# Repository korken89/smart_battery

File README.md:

# Testing repository for components of the Smart Charger project

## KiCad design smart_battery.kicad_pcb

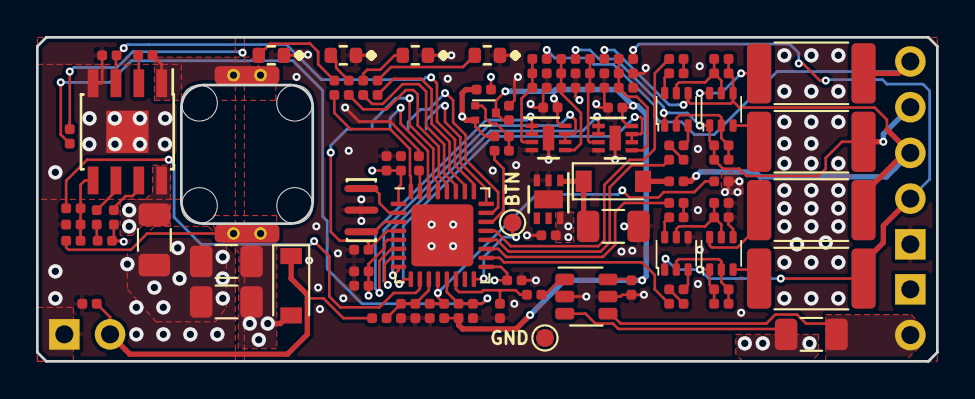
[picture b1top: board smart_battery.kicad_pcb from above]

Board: 4 copper layers, 50.0 x 18.0 mm, 102 parts (1 on the bottom side), 74 nets.

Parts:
C101, C102, C104, C106, C108, C109, C110, C111, C114, C201, C202, C203, C204, C205, C206, C207, C208, C209, C210, C211, C212, C213, C214, C301, C304: 0.1u; C_0402_1005Metric_Rounded
C103, C302, C305, C306: 22u; C_1206_3216Metric
C105, C107, C112, C113: 4.7u; C_0402_1005Metric_Rounded
C303: 2.7n; C_0402_1005Metric_Rounded
D101, D301: MBR0580S1-7; D_SOD-123
D102, D103, D104, D105: LED_Small; LEDC1608X60
D201, D202: BAT54SDW; SOT-363
FB101, FB102: BKH1005LM182-T; R_0402_1005Metric_Rounded
J101, J102: Conn_01x02_Male; 1x2_2.54mm
J103: Conn_01x05_Male; 1x5_2.54mm
J104: Dronecode_Debug; jst-sh-hor-6
J105, J106: Conn_01x01_Male; TestPoint_Pad_D1.0mm
L301: 10u; ASPI-0630LR-HOLE
Q101: RZM001P02T2L; SOT-723
Q201, Q202: PMGD280UN,115; SOT-363
R101, R102, R106, R304: 18k; R_0402_1005Metric_Rounded
R103: 50m; R_1206_3216Metric
R104, R213, R215, R217, R219: 1M; R_0402_1005Metric_Rounded
R105: 150k; R_0402_1005Metric_Rounded
R107, R109, R110, R111, R112, R113, R306: 2.5k; R_0402_1005Metric_Rounded
R108, R205, R206, R207, R208, R214, R216, R218, R220: 220k; R_0402_1005Metric_Rounded
R201, R202, R203, R204: 1k; R_0402_1005Metric_Rounded
R209, R210, R211, R212: 33; R_2512_6332Metric
R301, R302, R305: 47k; R_0402_1005Metric_Rounded
R303: 91k; R_0402_1005Metric_Rounded
TH101, TH102: 10k; R_0402_1005Metric_Rounded
U101: NCP716; DFN-6-1EP_2x2mm_P0.65mm_EP1x1.6mm
U102: STM32F051K6Ux; QFN-32-1EP_5x5mm_P0.5mm_EP3.45x3.45mm
U103: INA181; SOT-23-6
U202, U203: TSV912IQ2T; DFN-8-1EP_2x2mm_P0.45mm_EP0.64x1.38mm
U301: RT2862; SOIC-8-1EP_3.9x4.9mm_P1.27mm_EP2.35x2.35mm
Y101: PRQC8.00CR1010V00L; Resonator_3pin_3.2x1.3mm

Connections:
+3.3VA: C111.1, C112.1, FB101.2, Q101.2, R108.1, U102.5
+3V3: C105.1, C107.1, C109.1, C110.1, FB101.1, U101.6, U102.1, U102.17
/AMPS_ONOFF: R107.2, U102.22
/AMP_PWR: C104.2, C113.1, C213.2, C214.2, Q101.3, R101.2, R102.2, U103.6, U202.8, U203.8
/BAL1: R204.2, U102.18
/BAL2: R203.2, U102.19
/BAL3: R202.2, U102.20
/BAL4: R201.2, U102.21
/BATTERY: J101.2, R103.1, U103.4
/BOOT0: R106.1, U102.31
/BTN: J106.1, U102.16
/CELL1: C207.1, D202.1, J103.2, Q202.1, R207.2, R212.2, R213.2
/CELL2: C206.1, D201.4, FB102.2, J103.3, Q201.4, R206.2, R211.2, R215.2
/CELL3: C205.1, D201.1, J103.4, Q201.1, R205.2, R210.2, R217.2
/CELL4: J103.5, R209.2, R219.2
/DCDC_ENABLE: R301.2, U102.25, U301.3
/I_CHG: C114.2, R113.1, U102.14
/LED1: R109.1, U102.32
/LED2: R112.1, U102.28
/LED3: R111.1, U102.27
/LED4: R110.1, U102.26
/RST: C108.2, J104.1, U102.4
/RX: J104.3, U102.30
/SWCLK: J104.5, U102.24
/SWDIO: J104.4, U102.23
/TEMP1: C101.2, R101.1, TH101.1, U102.12
/TEMP2: C102.2, R102.1, TH102.1, U102.13
/TX: J104.2, U102.29
/VCELL1: U102.9, U203.6, U203.7
/VCELL2: U102.8, U203.1, U203.2
/VCELL3: U102.7, U202.6, U202.7
/VCELL4: U102.6, U202.1, U202.2
/VIN_CHG: C301.2, C302.2, D301.1, J102.2, R104.2, U301.8
/VIN_CHG_MEAS: C106.2, R104.1, R105.2, U102.11
/VSET: R304.2, U102.10
/buck_charger/BOOT: C304.2, U301.2
/buck_charger/COMP: C303.1, U301.6
/buck_charger/FB: R304.1, R305.2, R306.2, U301.5
/buck_charger/OUT_CHARGER: C305.2, C306.2, D301.2, L301.2, R103.2, R305.1, U103.3
/buck_charger/SW: C304.1, L301.1, U301.1
/cell_measurement_and_balancing/CELL1_G: C208.2, D202.5, Q202.5, R208.1
/cell_measurement_and_balancing/CELL2_G: C207.2, D202.2, Q202.2, R207.1
/cell_measurement_and_balancing/CELL3_G: C206.2, D201.5, Q201.5, R206.1
/cell_measurement_and_balancing/CELL4_G: C205.2, D201.2, Q201.2, R205.1
/cell_measurement_and_balancing/VCELL1: C209.2, R213.1, R214.2, U203.5
/cell_measurement_and_balancing/VCELL2: C210.2, R215.1, R216.2, U203.3
/cell_measurement_and_balancing/VCELL3: C211.2, R217.1, R218.2, U202.5
/cell_measurement_and_balancing/VCELL4: C212.2, R219.1, R220.2, U202.3
GND: C101.1, C102.1, C103.1, C104.1, C105.2, C106.1, C107.2, C108.1, C109.2, C110.2, C111.2, C112.2, C113.2, C114.1, C208.1, C209.1, C210.1, C211.1, C212.1, C213.1, C214.1, D102.1, D103.1, D104.1, D105.1, D202.4, J103.1, J104.0, J104.6, J105.1, Q202.4, R105.1, R106.2, R208.2, R214.1, R216.1, R218.1, R220.1, TH101.2, TH102.2, U101.2, U101.3, U101.7, U102.33, U103.2, U103.5, U202.4, U202.9, U203.4, U203.9, Y101.2
GNDPWR: C301.1, C302.1, C305.1, C306.1, J101.1, J102.1, R301.1, R302.2, R303.2, R306.1, U301.4, U301.9
unnamed: C103.2, D101.1, U101.1
unnamed: C201.1, R201.1
unnamed: C201.2, D201.6
unnamed: C202.1, R202.1
unnamed: C202.2, D201.3
unnamed: C203.1, R203.1
unnamed: C203.2, D202.6
unnamed: C204.1, R204.1
unnamed: C204.2, D202.3
unnamed: C303.2, R302.1
unnamed: D101.2, FB102.1
unnamed: D102.2, R109.2
unnamed: D103.2, R110.2
unnamed: D104.2, R111.2
unnamed: D105.2, R112.2
unnamed: Q101.1, R107.1, R108.2
unnamed: Q201.3, R210.1
unnamed: Q201.6, R209.1
unnamed: Q202.3, R212.1
unnamed: Q202.6, R211.1
unnamed: R113.2, U103.1
unnamed: R303.1, U301.7
unnamed: U102.2, Y101.1
unnamed: U102.3, Y101.3

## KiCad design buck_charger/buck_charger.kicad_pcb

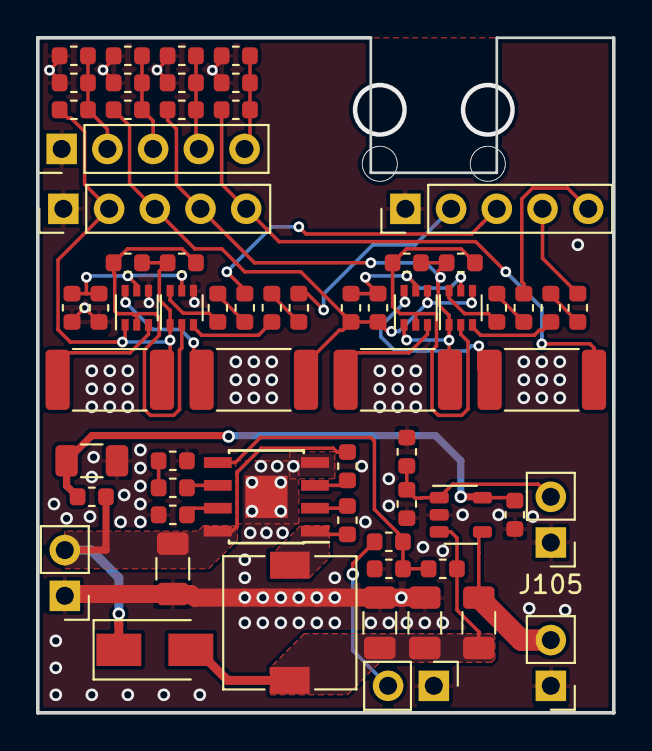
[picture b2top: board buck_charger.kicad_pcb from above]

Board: 2 copper layers, 32.0 x 37.5 mm, 64 parts (0 on the bottom side), 42 nets.

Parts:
C101, C104, C105, C106: 22u; C_1206_3216Metric
C102: 2.7n; C_0603_1608Metric
C103, C107, C108, C109, C110, C111, C112, C113, C114, C115, C116, C117, C118, C119, C120: 0.1u; C_0603_1608Metric
D101: VSSAF56-M3/6A; D_SMA
D102, D103: BAT54SDW; SOT-363_SC-70-6
J101, J102, J104, J105: Conn_01x02_Male; PinHeader_1x02_P2.54mm_Vertical
J103, J106, J107: Conn_01x05; PinHeader_1x05_P2.54mm_Vertical
L101: 10u; L_7.3x7.3_H3.5
Q101, Q102: PMGD280UN,115; SOT-363_SC-70-6
R101, R103, R108, R110, R116, R117, R118, R119, R125, R127, R129: 100k; R_0603_1608Metric
R102, R105: 47k; R_0603_1608Metric
R104: 18k; R_0603_1608Metric
R106: 2.5k; R_0603_1608Metric
R107: 50m; R_1206_3216Metric
R109, R124, R126, R128: 470k; R_0603_1608Metric
R111: 10; R_0603_1608Metric
R112, R113, R114, R115: 1k; R_0603_1608Metric
R120, R121, R122, R123: 33; R_2512_6332Metric
U101: RT2862; SOIC-8-1EP_3.9x4.9mm_P1.27mm_EP2.35x2.35mm
U102: INA138; SOT-23-5

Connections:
/BOOT: C103.2, U101.2
/CELL1: C116.1, D103.1, J106.2, Q102.1, R118.2, R123.2, R128.2
/CELL1_G: C117.2, D103.5, Q102.5, R119.1
/CELL2: C115.1, D102.4, J106.3, Q101.4, R117.2, R122.2, R126.2
/CELL2_G: C116.2, D103.2, Q102.2, R118.1
/CELL3: C114.1, D102.1, J106.4, Q101.1, R116.2, R121.2, R124.2
/CELL3_G: C115.2, D102.5, Q101.5, R117.1
/CELL4: J106.5, R109.2, R120.2
/CELL4_G: C114.2, D102.2, Q101.2, R116.1
/CHG_OUT: C104.2, C106.2, D101.2, L101.2, R105.1, R107.2, U102.3
/COMP: C102.1, U101.6
/DRIVE1: J103.2, R115.2
/DRIVE2: J103.3, R114.2
/DRIVE3: J103.4, R113.2
/DRIVE4: J103.5, R112.2
/FB: R104.1, R105.2, R106.2, U101.5
/IMEAS: C108.2, J105.2, R108.2, U102.1
/SW: C103.1, L101.1, U101.1
/VCELL1: C120.2, J107.2, R128.1, R129.2
/VCELL2: C119.2, J107.3, R126.1, R127.2
/VCELL3: C118.2, J107.4, R124.1, R125.2
/VCELL4: C109.2, J107.5, R109.1, R110.2
/VIN: C101.2, D101.1, J101.2, R101.1, R111.1, U101.8
/VOUT: J104.2, R107.1, U102.4
/VSET: J102.2, R104.2
GND: C101.1, C104.1, C105.1, C106.1, C107.1, C108.1, C109.1, C117.1, C118.1, C119.1, C120.1, D103.4, J101.1, J102.1, J103.1, J104.1, J105.1, J106.1, J107.1, Q102.4, R102.2, R103.2, R106.1, R108.1, R110.1, R119.2, R125.1, R127.1, R129.1, U101.4, U101.9, U102.2
unnamed: C102.2, R102.1
unnamed: C105.2, C107.2, R111.2, U102.5
unnamed: C110.1, R112.1
unnamed: C110.2, D102.6
unnamed: C111.1, R113.1
unnamed: C111.2, D102.3
unnamed: C112.1, R114.1
unnamed: C112.2, D103.6
unnamed: C113.1, R115.1
unnamed: C113.2, D103.3
unnamed: Q101.3, R121.1
unnamed: Q101.6, R120.1
unnamed: Q102.3, R123.1
unnamed: Q102.6, R122.1
unnamed: R101.2, U101.3
unnamed: R103.1, U101.7

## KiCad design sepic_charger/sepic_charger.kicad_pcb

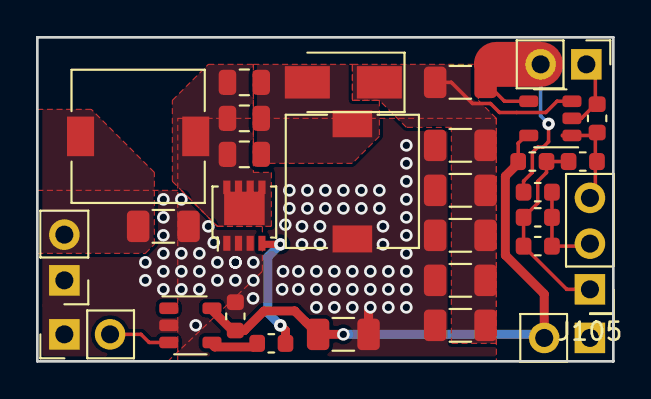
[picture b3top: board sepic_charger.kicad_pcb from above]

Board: 2 copper layers, 32.0 x 18.0 mm, 30 parts (0 on the bottom side), 12 nets.

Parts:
C1, C105, C111, C112: 0.1u; C_0603_1608Metric
C101, C106, C107, C108, C109, C110, C113: 22u; C_1206_3216Metric
C102, C103, C104: 4.7u; C_0805_2012Metric
D101: VSSAF56-M3/6A; D_SMA
J101, J102, J104, J106: Conn_01x02_Male; PinHeader_1x02_P2.54mm_Vertical
J105: Conn_01x03_Male; PinHeader_1x03_P2.54mm_Vertical
L101, L102: 10u; L_7.3x7.3_H3.5
Q101: NVTFS5C673NLTAG; LFPAK33
R1, R104: 100k; R_0603_1608Metric
R2: 22k; R_0603_1608Metric
R101: 2.2; R_0603_1608Metric
R103: 50m; R_1206_3216Metric
U101: INA138; SOT-23-5
U102: UCC2751x; SOT-23-5

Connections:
+5V: C105.1, C111.2, C113.2, J106.2, U101.5, U102.5
/GATE: Q101.4, R101.1
/IMEAS: C112.2, J105.3, R104.2, U101.1
/SEPIC_OUT: C106.2, C107.2, C108.2, C109.2, C110.2, D101.1, R103.2, U101.3
/SW: C102.2, C103.2, C104.2, L101.2, Q101.5
/SW2: C102.1, C103.1, C104.1, D101.2, L102.1
/VIN: C101.2, J101.2, L101.1
/VMEAS: C1.2, J105.2, R1.1, R2.2
/VOUT: J104.2, R1.2, R103.1, U101.4
GND: C1.1, C101.1, C105.2, C106.1, C107.1, C108.1, C109.1, C110.1, C111.1, C112.1, C113.1, J101.1, J102.1, J104.1, J105.1, J106.1, L102.2, Q101.1, Q101.2, Q101.3, R2.1, R104.1, U101.2, U102.2
unnamed: J102.2, U102.3
unnamed: R101.2, U102.4

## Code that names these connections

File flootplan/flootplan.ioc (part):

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Mcu.Name=STM32F051K8Ux
Mcu.Package=UFQFPN32
Mcu.UserName=STM32F051K8Ux
PA0.GPIOParameters=GPIO_Label
PA0.GPIO_Label=VCELL (AIN0)
PA0.Mode=IN0
PA0.Signal=ADC_IN0
PA1.GPIOParameters=GPIO_Label
PA1.GPIO_Label=VCELL (AIN1)
PA1.Mode=IN1
PA1.Signal=ADC_IN1
PA10.GPIOParameters=GPIO_Label
PA10.GPIO_Label=BAL (TIM1_CH3)
PA10.Signal=S_TIM1_CH3
PA11.GPIOParameters=GPIO_Label
PA11.GPIO_Label=BAL (TIM1_CH4)
PA11.Signal=S_TIM1_CH4
PA13.Mode=Serial_Wire
PA13.Signal=SYS_SWDIO
PA14.Mode=Serial_Wire
PA14.Signal=SYS_SWCLK
PA2.GPIOParameters=GPIO_Label
PA2.GPIO_Label=VCELL (AIN2)
PA2.Mode=IN2
PA2.Signal=ADC_IN2
PA3.GPIOParameters=GPIO_Label
PA3.GPIO_Label=VCELL (AIN3)
PA3.Mode=IN3
PA3.Signal=ADC_IN3
PA4.GPIOParameters=GPIO_Label
PA4.GPIO_Label=VSET (DAC1)
PA4.Signal=COMP_DAC11_group
PA5.GPIOParameters=GPIO_Label
PA5.GPIO_Label=VIN_CHG (AIN5)
PA5.Mode=IN5
PA5.Signal=ADC_IN5
PA6.GPIOParameters=GPIO_Label
PA6.GPIO_Label=I_CHG (AIN6)
PA6.Mode=IN6
PA6.Signal=ADC_IN6
PA7.GPIOParameters=GPIO_Label
PA7.GPIO_Label=TEMP1 (AIN7)
PA7.Mode=IN7
PA7.Signal=ADC_IN7
PA8.GPIOParameters=GPIO_Label
PA8.GPIO_Label=BAL (TIM1_CH1)
PA8.Signal=S_TIM1_CH1
PA9.GPIOParameters=GPIO_Label
PA9.GPIO_Label=BAL (TIM1_CH2)
PA9.Signal=S_TIM1_CH2
PB0.GPIOParameters=GPIO_Label
PB0.GPIO_Label=TEMP2 (AIN8)
PB0.Mode=IN8
PB0.Signal=ADC_IN8
PB1.GPIOParameters=GPIO_Label
PB1.GPIO_Label=TEMP3 (AIN9)
PB1.Mode=IN9
PB1.Signal=ADC_IN9
PB6.Mode=Asynchronous
PB6.Signal=USART1_TX
PB7.Mode=Asynchronous
PB7.Signal=USART1_RX
PB8.Signal=S_TIM16_CH1
PF0-OSC_IN.Mode=HSE-External-Oscillator
PF0-OSC_IN.Signal=RCC_OSC_IN
PF1-OSC_OUT.Mode=HSE-External-Oscillator
PF1-OSC_OUT.Signal=RCC_OSC_OUT
RCC.SYSCLKFreq_VALUE=8000000
RCC.SYSCLKSource=RCC_SYSCLKSOURCE_HSE
board=custom

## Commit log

2018-11-22 Updated design
2018-11-22 Minor changes
2018-12-12 Started buck version
2018-12-13 Updated sub modules
2018-12-13 More stuff
2019-01-03 Schematic done
2019-01-03 Added PCB
2019-01-03 Layer, track and mask setup
2019-01-03 Floorplan update
2019-01-07 More work
2019-01-08 Started PCB layout
2019-01-14 More layout and fixes
2019-01-15 Minor layout updates
2019-01-29 Added some silkscreen
2019-02-12 Added button
